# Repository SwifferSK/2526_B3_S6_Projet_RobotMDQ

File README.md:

<!-- ===================================================== -->
<!--                        HERO                            -->
<!-- ===================================================== -->

<!-- ===================================================== -->
<!--                       BADGES                           -->
<!-- ===================================================== -->

<p align="center">

</p>

<p align="center">

</p>

---
## 🧭 Menu
- [Présentation](#présentation)
- [Fonctionnalités](#fonctionnalités)
- [Structure du dépôt](#structure-du-dépôt-branches)
- [Architecture](#architecture)
- [Hardware](#hardware)
- [Dashboard](#dashboard)
- [Demo](#demo)
- [Équipe](#équipe)

---

## Présentation

Ce projet consiste à concevoir un **robot autonome bipède** capable de suivre une ligne tracée au sol.        

Le robot utilise ses **capteurs** pour comprendre sa position et ajuste en permanence ses **moteurs** afin de ne pas tomber pendant le déplacement.

L’ensemble du système est contrôlé par une **Raspberry Pi Zero 2W**, qui traite les informations et prend les décisions en temps réel.

---

## Fonctionnalités
<div align="center">
  <table align="center" cellspacing="0" cellpadding="14">
    <tr>
      <td width="300" align="center" valign="top">
        <h3>🛤️ Suivi de ligne</h3>
        <p>
          Détection du trajet via des photorésistances/ligne<br/>
          Seuils + calibration<br/>
          Lecture analogique via ADC
        </p>
      </td>
      <td width="300" align="center" valign="top">
        <h3>🧠 Stabilisation </h3>
        <p>
          IMU (acc + gyro)<br/>
          Filtrage <br/>
          Donnée envoyer en I2C au MCU<br/>
        </p>
      </td>
      <td width="300" align="center" valign="top">
        <h3>⚙️ Contrôle</h3>
        <p>
          Boucle temps réel (PID prévu)<br/>
          Commande moteurs fluide<br/>
          Sécurités (tilt / cutoff)
        </p>
      </td>
    </tr>
  </table>
</div>

---
##  Structure du Dépôt (Branches)

Le projet est organisé de manière modulaire. La branche `main` contient le système complet, tandis que les branches de développement permettent de tester chaque composant indépendamment :

* **`main`** : Schéma électrique complet,
* **`Kicad_RPI_IMU`** :Schéma électrique de l'**IMU LSM6DSOX**.
* **`Kicad_MCP3208`** : Schéma électrique du **MCP3208** et lecture des photorésistances pour la détection de ligne.
* **`Kicad_TMC2225`** : Schéma électrique de **TMC2225** pour le contrôle des moteurs pas à pas. .
* **`merged-code`** : Fusion des 3 firmwares.
* **`Firmware_MCP3208`** : Firmmware du **MCP3208**.
* **`Firmware_LSM6DSOX`** :Firmmware du l'**IMU LSM6DSOX**.
* **`Firmware_TMC2225`** : Firmmware du **TMC2225** .
---

## Architecture

<div align="center">

  <tr>
    <td width="540" valign="top">
      <h3 align="center">🔌 Chaîne matérielle</h3>
      <p align="center">
        Capteurs optiques → <b>MCP3208 (ADC)</b><br/>
        IMU → <b>I2C/SPI</b> → <b>Raspberry Pi Zero 2W</b><br/>
        RPi → <b>GPIO</b> → <b>TMC2225</b> → Moteurs pas à pas
      </p>
    </td>
    <td width="540" valign="top">
      <h3 align="center">🧠 Chaîne de contrôle</h3>
      <p align="center">
        Acquisition → Filtrage → Estimation<br/>
        Contrôle (PID) → Commande moteurs<br/>
      </p>
    </td>
  </tr>

</div>

---

## Hardware

<div align="center">

<table align="center">
  <tr>
    <th align="left">Composant</th>
    <th align="left">Rôle</th>
    <th align="left">Interface</th>
  </tr>
  <tr>
    <td><b>Raspberry Pi Zero 2W</b></td>
    <td>Contrôleur principal</td>
    <td>GPIO / SPI / I2C</td>
  </tr>
  <tr>
    <td><b>LSM6DSOX</b></td>
    <td>IMU (acc + gyro)</td>
    <td>I2C / SPI</td>
  </tr>
  <tr>
    <td><b>MCP3208</b></td>
    <td>Convertisseur ADC</td>
    <td>SPI</td>
  </tr>
  <tr>
    <td><b>TMC2225 (x2)</b></td>
    <td>Drivers moteurs pas à pas</td>
    <td>STEP / DIR</td>
  </tr>
  <tr>
    <td><b>Capteurs optiques</b></td>
    <td>Détection de ligne</td>
    <td>Analogique</td>
  </tr>
</table>

</div>

---

## Dashboard
<div align="center">

<p align="center">

</p>

  </a>

</p>

<table align="center">
  <tr>
    <td align="center" width="520">
      
    </td>
   
  </tr>
</table>

</div>

---

## Demo

<p align="center">
  <!--  -->
</p>

---

## Équipe

<p align="center">
  <b> Damien Theas • Manel Benboujemaa  • Quentin Bechler</b><br/>
  <sub>Bachelor ENSEA — Robotique • Design matériel</sub>
</p>

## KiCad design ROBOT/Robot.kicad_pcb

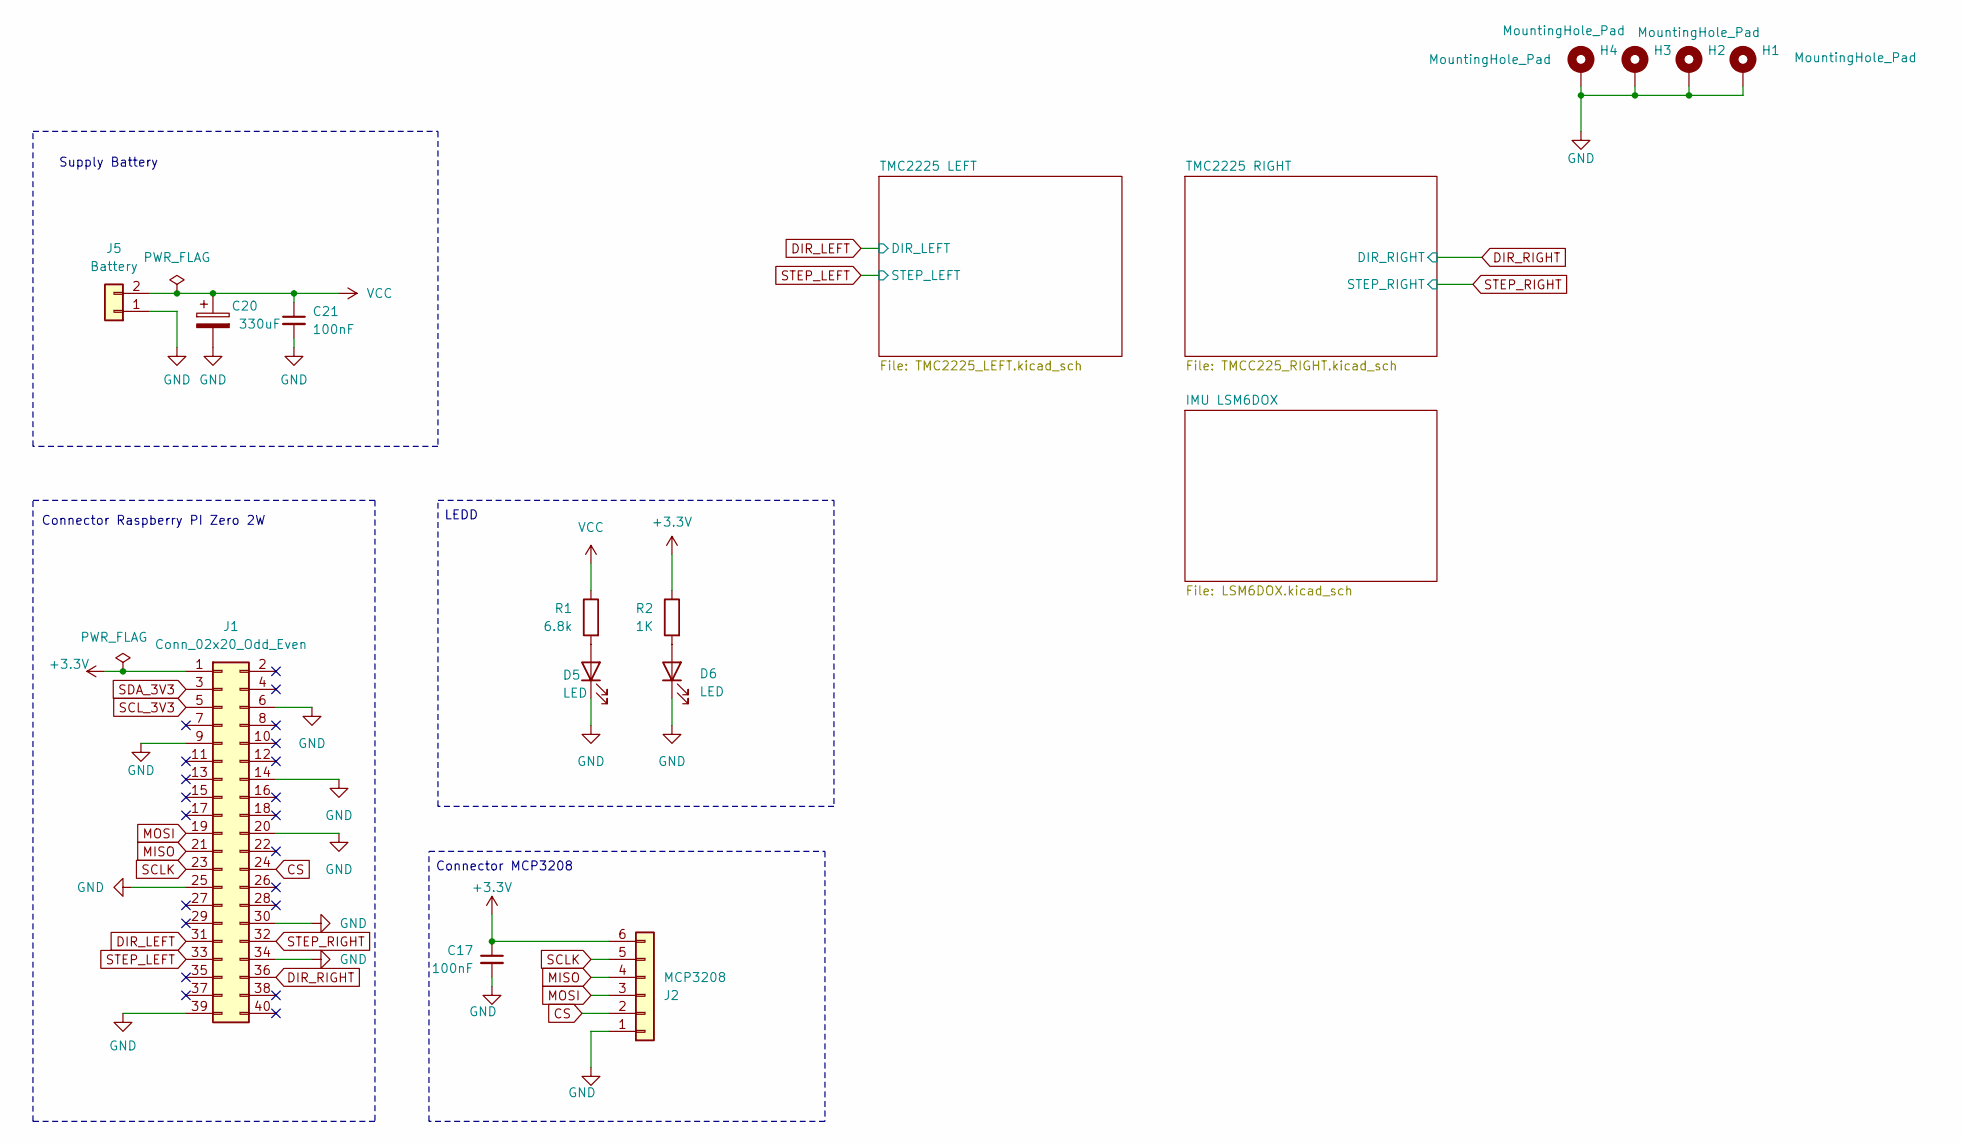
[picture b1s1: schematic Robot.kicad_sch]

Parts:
C17: 100nF; C_0603_1608Metric_Pad1.08x0.95mm_HandSolder
C20: 330uF; CP_Elec_6.3x5.4
C21: 100nF; C_0805_2012Metric_Pad1.18x1.45mm_HandSolder
D5, D6: LED; LED_0603_1608Metric_Pad1.05x0.95mm_HandSolder
H1, H2, H3, H4: MountingHole_Pad; MountingHole_2.7mm_M2.5_Pad
J1: Conn_02x20_Odd_Even; PinSocket_2x20_P2.54mm_Vertical
J2: MCP3208; JST_PH_B6B-PH-K_1x06_P2.00mm_Vertical
J5: Battery; JST_EH_B2B-EH-A_1x02_P2.50mm_Vertical
R1: 6.8k; R_0603_1608Metric_Pad0.98x0.95mm_HandSolder
R2: 1K; R_0603_1608Metric_Pad0.98x0.95mm_HandSolder

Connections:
+3.3V: C17.1, J1.1, J2.6, R2.1; also elsewhere on the board
CS: J1.24, J2.2
DIR_LEFT: J1.31; also elsewhere on the board
DIR_RIGHT: J1.36; also elsewhere on the board
GND: C17.2, C20.2, C21.2, D5.1 (K), D6.1 (K), H1.1, H2.1, H3.1, H4.1, J1.6, J1.9, J1.14, J1.20, J1.25, J1.30, J1.34, J1.39, J2.1, J5.1; also elsewhere on the board
MISO: J1.21, J2.4
MOSI: J1.19, J2.3
unnamed: D5.2 (A), R1.2
unnamed: D6.2 (A), R2.2
SCLK: J1.23, J2.5
SCL_3V3: J1.5; also elsewhere on the board
SDA_3V3: J1.3; also elsewhere on the board
STEP_LEFT: J1.33; also elsewhere on the board
STEP_RIGHT: J1.32; also elsewhere on the board
VCC: C20.1, C21.1, J5.2, R1.1; also elsewhere on the board

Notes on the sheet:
Supply Battery
Connector MCP3208
Connector Raspberry PI Zero 2W
LEDD

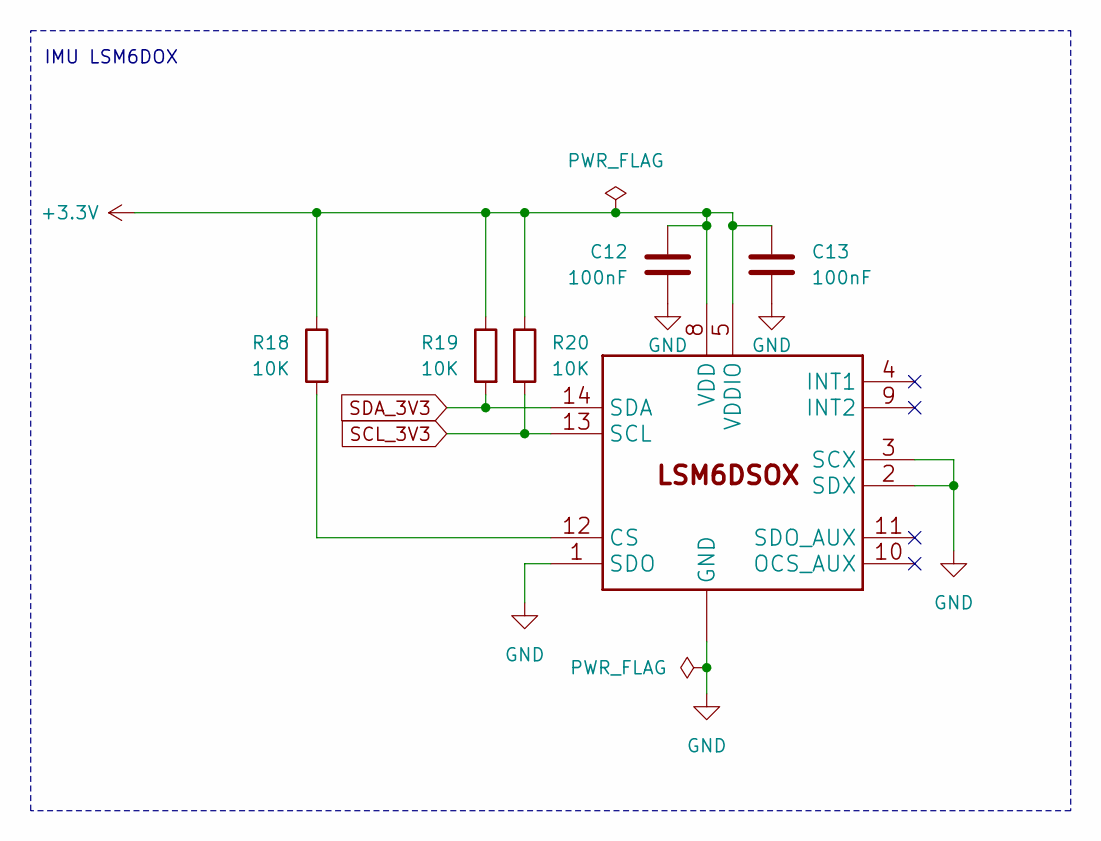
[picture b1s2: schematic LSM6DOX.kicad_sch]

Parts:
C12, C13: 100nF; C_0603_1608Metric_Pad1.08x0.95mm_HandSolder
R18, R19, R20: 10K; R_0603_1608Metric_Pad0.98x0.95mm_HandSolder
U$1: LSM6DSOX; LGA-14_3x2.5mm_P0.5mm_LayoutBorder3x4y

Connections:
+3.3V: C12.2, C13.2, R18.1, R19.1, R20.1, U$1.5 (VDDIO), U$1.8 (VDD); also elsewhere on the board
GND: C12.1, C13.1, U$1.1 (SDO), U$1.2 (SDX), U$1.3 (SCX), U$1.6 (GND), U$1.7 (GND); also elsewhere on the board
unnamed: R18.2, U$1.12 (CS)
SCL_3V3: R20.2, U$1.13 (SCL); also elsewhere on the board
SDA_3V3: R19.2, U$1.14 (SDA); also elsewhere on the board

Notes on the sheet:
IMU LSM6DOX

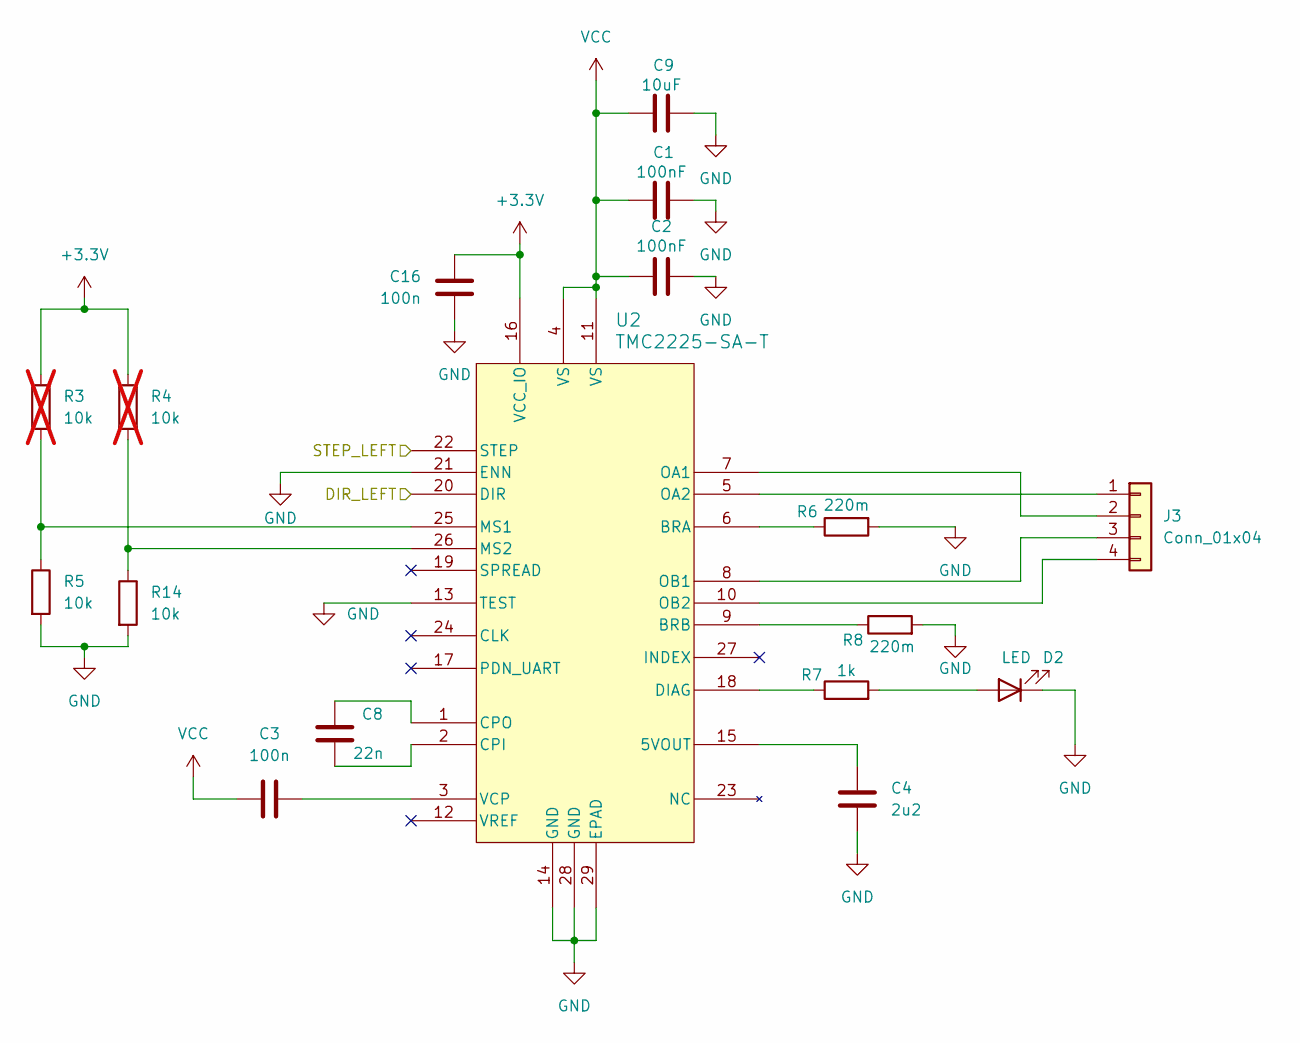
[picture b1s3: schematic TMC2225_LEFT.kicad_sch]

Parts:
C1, C2: 100nF; C_0805_2012Metric_Pad1.18x1.45mm_HandSolder
C3, C16: 100n; C_0603_1608Metric_Pad1.08x0.95mm_HandSolder
C4: 2u2; C_0603_1608Metric_Pad1.08x0.95mm_HandSolder
C8: 22n; C_0603_1608Metric_Pad1.08x0.95mm_HandSolder
C9: 10uF; C_0805_2012Metric_Pad1.18x1.45mm_HandSolder
D2: LED; LED_0603_1608Metric_Pad1.05x0.95mm_HandSolder
J3: Conn_01x04; JST_PH_B4B-PH-K_1x04_P2.00mm_Vertical
R3, R4: 10k; R_0603_1608Metric_Pad0.98x0.95mm_HandSolder; not fitted
R5, R14: 10k; R_0603_1608Metric_Pad0.98x0.95mm_HandSolder
R6, R8: 220m; R_1206_3216Metric_Pad1.30x1.75mm_HandSolder
R7: 1k; R_0603_1608Metric_Pad0.98x0.95mm_HandSolder
U2: TMC2225-SA-T; HTSSOP-28-1EP_4.4x9.7mm_P0.65mm_EP2.85x5.4mm_ThermalVias

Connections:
+3.3V: C16.2, R3.1, R4.1, U2.16 (VCC_IO); also elsewhere on the board
DIR_LEFT: U2.20 (DIR); also elsewhere on the board
GND: C1.2, C2.2, C4.2, C9.2, C16.1, D2.1 (K), R5.2, R6.2, R8.2, R14.2, U2.13 (TEST), U2.14 (GND), U2.21 (ENN), U2.28 (GND), U2.29 (EPAD); also elsewhere on the board
unnamed: D2.2 (A), R7.2
unnamed: J3.1, U2.5 (OA2)
unnamed: J3.2, U2.7 (OA1)
unnamed: J3.3, U2.8 (OB1)
unnamed: J3.4, U2.10 (OB2)
unnamed: C4.1, U2.15 (5VOUT)
unnamed: R6.1, U2.6 (BRA)
unnamed: R8.1, U2.9 (BRB)
unnamed: C8.2, U2.2 (CPI)
unnamed: C8.1, U2.1 (CPO)
unnamed: R7.1, U2.18 (DIAG)
unnamed: R3.2, R5.1, U2.25 (MS1)
unnamed: R4.2, R14.1, U2.26 (MS2)
unnamed: C3.2, U2.3 (VCP)
STEP_LEFT: U2.22 (STEP); also elsewhere on the board
VCC: C1.1, C2.1, C3.1, C9.1, U2.4 (VS), U2.11 (VS); also elsewhere on the board

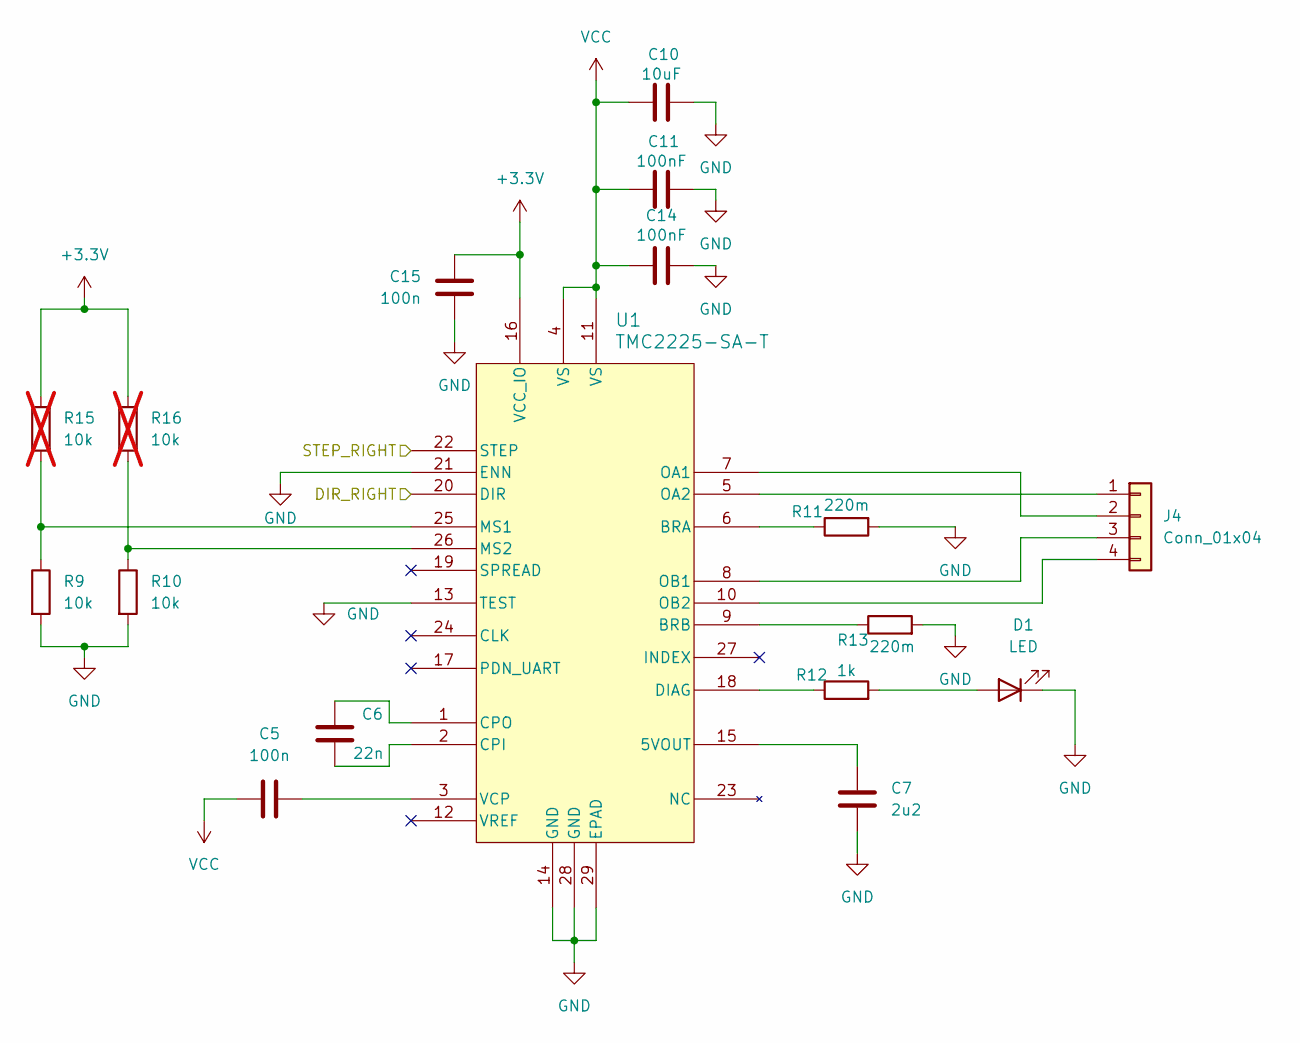
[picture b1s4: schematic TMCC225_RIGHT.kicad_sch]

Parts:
C5, C15: 100n; C_0603_1608Metric_Pad1.08x0.95mm_HandSolder
C6: 22n; C_0603_1608Metric_Pad1.08x0.95mm_HandSolder
C7: 2u2; C_0603_1608Metric_Pad1.08x0.95mm_HandSolder
C10: 10uF; C_0805_2012Metric_Pad1.18x1.45mm_HandSolder
C11, C14: 100nF; C_0603_1608Metric_Pad1.08x0.95mm_HandSolder
D1: LED; LED_0603_1608Metric_Pad1.05x0.95mm_HandSolder
J4: Conn_01x04; JST_PH_B4B-PH-K_1x04_P2.00mm_Vertical
R9, R10: 10k; R_0603_1608Metric_Pad0.98x0.95mm_HandSolder
R11, R13: 220m; R_1206_3216Metric_Pad1.30x1.75mm_HandSolder
R12: 1k; R_0603_1608Metric_Pad0.98x0.95mm_HandSolder
R15, R16: 10k; R_0603_1608Metric_Pad0.98x0.95mm_HandSolder; not fitted
U1: TMC2225-SA-T; HTSSOP-28-1EP_4.4x9.7mm_P0.65mm_EP2.85x5.4mm_ThermalVias

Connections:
+3.3V: C15.2, R15.1, R16.1, U1.16 (VCC_IO); also elsewhere on the board
DIR_RIGHT: U1.20 (DIR); also elsewhere on the board
GND: C7.2, C10.2, C11.2, C14.2, C15.1, D1.1 (K), R9.2, R10.2, R11.2, R13.2, U1.13 (TEST), U1.14 (GND), U1.21 (ENN), U1.28 (GND), U1.29 (EPAD); also elsewhere on the board
unnamed: D1.2 (A), R12.2
unnamed: J4.1, U1.5 (OA2)
unnamed: J4.2, U1.7 (OA1)
unnamed: J4.3, U1.8 (OB1)
unnamed: J4.4, U1.10 (OB2)
unnamed: C7.1, U1.15 (5VOUT)
unnamed: R11.1, U1.6 (BRA)
unnamed: R13.1, U1.9 (BRB)
unnamed: C6.2, U1.2 (CPI)
unnamed: C6.1, U1.1 (CPO)
unnamed: R12.1, U1.18 (DIAG)
unnamed: R9.1, R15.2, U1.25 (MS1)
unnamed: R10.1, R16.2, U1.26 (MS2)
unnamed: C5.2, U1.3 (VCP)
STEP_RIGHT: U1.22 (STEP); also elsewhere on the board
VCC: C5.1, C10.1, C11.1, C14.1, U1.4 (VS), U1.11 (VS); also elsewhere on the board

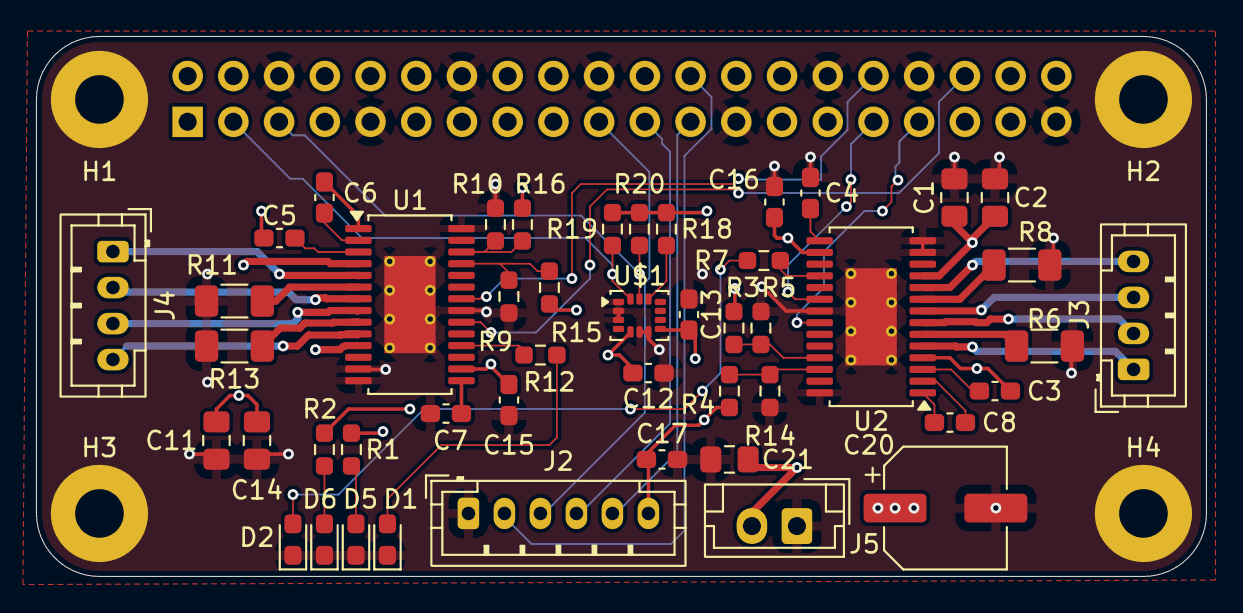
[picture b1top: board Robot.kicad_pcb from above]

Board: 4 copper layers, 65.0 x 30.0 mm, 52 parts (1 on the bottom side), 44 nets.

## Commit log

2026-01-20 inventaire.md
2026-01-20 Add Datasheets Folder and LSM6DOX Datasheets
2026-01-20 Schema KiCad for IMU
    90% schema complet
    Conne02X20 for RPI
    footprint missing for IMU
2026-01-21 Add buck 3V3 converter
    Add buck 3V3 converter
2026-01-21 update schema IMU
    remove buck converter
2026-01-21 Schema Kicad Connecteur MCP
2026-01-21 Schema KiCad ROBOT
    Schema KiCad ROBOT
2026-01-21 add DC-DC BUCK + LED
    add DC-DC BUCK + LED
2026-01-21 Add Backup
2026-01-21 Revise README
    Updated project description, features, and hardware details in README.
2026-01-23 correction schéma
    correction schéma
2026-01-23 add footprint
2026-01-23 Drawing
2026-01-23 Schema OK
2026-01-23 edge cut cotation
2026-01-23 Update PCB
2026-01-23 backup
2026-01-24 First Routage
2026-01-25 Schema PCB no error
2026-01-25 Update backup
2026-01-25 GND PAD 29 TMC22225
2026-01-26 Update PCB routage
2026-01-26 bannière
2026-01-26 Piste puissance + via GND
2026-01-26 add datasheet in documentation
2026-01-26 PCB 3D
2026-01-26 NETCLASS Update
2026-01-26 Update netclass
2026-01-26 add condo
2026-01-26 Correct spelling of Damien Théas to Damien THEAS
2026-01-26 Revue de shcema
2026-01-26 remove python
2026-01-26 PCB style
2026-01-26 stach
2026-01-26 update silkscreen
2026-01-26 update MPN
2026-01-26 B.silkscreen Text + Logo
2026-01-26 Gerber file
2026-01-26 Update B.silkscreen text + logo
2026-01-26 Gerber
2026-01-30 Ajout code mergé
2026-02-17 Revise README for robot project details
    Updated project description and functionality details.
2026-02-17 Revise project overview and add repository structure
    Updated project description and features in README.md. Added repository structure and clarified sensor descriptions.
2026-02-17 lien clickable.md
2026-03-17 apdate code correction motor driver
2026-03-17 error variable undefided
2026-03-17 test code
2026-03-17 filtre
2026-03-18 c'est la bonne
2026-03-18 Update main_imu.py
    test
2026-03-18 Revert "Update main_imu.py"
    This reverts commit e31848338ca73519aa463d70c6e562ae6c21c598.
2026-03-18 Reapply "Update main_imu.py"
    This reverts commit 0890f95c1aad3174d9bdbe7190a092627d7d42c1.
2026-03-18 derrg
2026-03-18 Revert "c'est la bonne"
    This reverts commit 4905f158c418bc40ed2ca5e2bd4746439e91663b.
2026-03-18 Revert "Update main_imu.py"
    This reverts commit de2211d23fbbb6c4abf0b4b418d1877a6825d206.
2026-03-18 delete
2026-03-18 Test
2026-03-18 last chance
2026-03-18 math
    efef
2026-03-18 KP 5 speed 500
2026-03-20 zerg
2026-04-15 ergfgg
2026-04-17 Refactor line follower logic and remove comments
2026-04-17 Presentation robot MDQ PPT 17/04/26
